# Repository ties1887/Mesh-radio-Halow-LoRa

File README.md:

# Mesh Radio

Open-source 3D-printable radio enclosures for Wi-Fi HaLow, MANET and LoRa experiments.

This repository contains CAD files, printable files, hardware references and short build notes. It is a DIY hardware/CAD release, not a full step-by-step wiring guide. Builders should verify fit, wiring, polarity, cooling, antenna mounting and power setup for their own hardware.

> [!TIP]
> **Support this project**  
> I am a **21-year-old full-time student** building this in my spare time. If this work helps you, donations help fund parts, prototypes and testing.  
> **[Support me on Ko-fi](https://ko-fi.com/ties1887)**

## Contents

- [Choose your build](#choose-your-build)
- [Standalone battery pack](#standalone-battery-pack)
- [What the files are for](#what-the-files-are-for)
- [Build notes](#build-notes)
- [Bill of materials](#bill-of-materials)
- [Planned builds](#planned-builds)
- [Software](#software)
- [Contributing and support](#contributing-and-support)
- [License](#license)

## Choose your build

| Build | Generation | Main hardware | Files |
|---|---|---|---|
| **[P4-Wio](./Second-Generation-Builds/P4-Wio/)** | Second generation | Raspberry Pi 4 + WM1302 Pi HAT + Wio-WM6108 | 3MF, STEP, SolidWorks 2025 |
| **[CM4 Carrier Board](./Second-Generation-Builds/CM4-Carrier-Board/)** | Second generation, development | Raspberry Pi CM4 + M.2 E-key Wi-Fi + optional MM8108 HaLow | KiCad source, local libraries, 3D models, review report |
| **[V3](./First-Generation-Builds/V3_18-6-2026/)** | First generation | Raspberry Pi 4 + WM1302 Pi HAT + Wio-WM6108 + RAK WisMesh 1W kit | 3MF, STEP, SolidWorks 2023/2025 |
| **[V2](./First-Generation-Builds/V2_30-5-2026/)** | First generation | Raspberry Pi 4 + WM1302 Pi HAT + Wio-WM6108 + RAK WisMesh 1W kit | 3MF, STL, STEP, SolidWorks 2023/2025 |
| **[V1](./First-Generation-Builds/V1_5-5-2026/)** | First generation | Raspberry Pi 4 + WM1302 Pi HAT + Wio-WM6108 + RAK WisMesh 1W kit | 3MF, STEP, SolidWorks 2023/2025 |

V1, V2 and V3 are still valid first generation builds. They may need more fitting or manual finishing, but they have been built, printed and used.

> [!CAUTION]
> **HaLow and LoRa together:** early tests with Wi-Fi HaLow and LoRa/Meshtastic running at the same time did not work well. The radios appeared to interfere with each other, even when using different channels. These tests were limited, so this is not a final RF conclusion, but builders should not expect HaLow and LoRa to work perfectly together without extra testing or design changes. Treat LoRa as a fallback/secondary system unless you have verified your own setup.

## Standalone battery pack

The **[Twist-Lock Battery Pack](./Twist-Lock-Battery-Pack/)** is a separate design, not part of only one build.

It is intended as a shared battery-pack design for both:

- first generation builds;
- second generation builds.

Available files include 3MF, STEP, STL and SolidWorks 2025 source archive.

## What the files are for

| File type | Use |
|---|---|
| `3MF` | Preferred print/project files for slicers |
| `STL` | Individual mesh exports when available |
| `STEP` | CAD exchange files for inspection, remixing or non-SolidWorks workflows |
| `SolidWorks` / `.zip` | Native source files or complete SolidWorks archives |

Download the complete build folder before opening a SolidWorks assembly so referenced parts remain available.

## Build notes

- **P4-Wio** is the current second generation build. It uses a Raspberry Pi 4, WM1302 Pi HAT style adapter and Seeed Studio Wio WM6108 Wi-Fi HaLow module.
- **P4-Wio is HaLow-only.** It does not include the separate LoRa/Meshtastic subsystem from the first generation prototypes.
- **V1** uses an integrated battery layout.
- **V2 and V3** use a removable twist-lock battery layout.
- **CM4 Carrier Board** source files are available for review and collaboration, but the design is not yet released for fabrication. Read its production-check report before making hardware.

<details>
<summary><strong>Prototype component and power-flow reference</strong></summary>

<br>

This is a prototype reference for component relationships and power flow. It combines ideas from different versions and is not a final wiring guide.

</details>

<details>
<summary><strong>Prototype wiring reference</strong></summary>

<br>

This image documents prototype wiring. Verify every connection against the exact version and modules you are building.

</details>

## Bill of materials

The shared BOM contains parts used across multiple prototypes. **Do not order every listed part.** Check the build you are making first.

**[Open the current shared BOM](https://docs.google.com/spreadsheets/d/1Nt8EjYsgWTId0Qjl1BAAxPci3bh1FSZ7VQxQRFxyHnk/edit?usp=sharing)**

Supplier links, prices and availability may change. Confirm dimensions, connector type, voltage range and module version before ordering.

## Planned builds

<details>
<summary><strong>Future build names and targets</strong></summary>

<br>

| Build | Hardware target | Notes |
|---|---|---|
| `P4-LongWave` | Raspberry Pi 4 + Lunpid/LongWave MM8108 USB HaLow | Planned Pi 4 USB HaLow build |
| `C4-LongWave` | Raspberry Pi CM4 + Lunpid/LongWave MM8108 USB HaLow | Planned compact CM4 build |
| `C4-DualMesh` | Raspberry Pi CM4 + MM8108 HaLow + MT7916EUD | Research path for HaLow plus 2.4/5/6 GHz mesh |

```text
P4 = Raspberry Pi 4
C4 = Raspberry Pi Compute Module 4
Wio = Seeed Studio Wio WM6108 HaLow
LongWave = Lunpid/LongWave MM8108 USB HaLow
DualMesh = MM8108 HaLow plus MT7916EUD for 2.4/5/6 GHz mesh
```

A planned build should get its own folder when it has a selected hardware stack, CAD layout, printable/exported files and a short build README.

</details>

## Software

Software installation and support are provided by the upstream projects:

- **[OpenMANET documentation](https://openmanet.github.io/docs/)**
- **[OpenMANET firmware](https://github.com/OpenMANET/firmware)**
- **[Meshtastic documentation](https://meshtastic.org/docs/)**
- **[Meshtastic firmware](https://github.com/meshtastic/firmware)**

OpenMANET, Meshtastic and third-party hardware remain subject to their own licenses, documentation and support policies.

## Contributing and support

Questions, measurements, test results, issue reports, documentation corrections and design improvements are welcome.

- **[Open an issue](https://github.com/ties1887/Mesh-radio-Halow-LoRa/issues)**
- **[Create a pull request](https://github.com/ties1887/Mesh-radio-Halow-LoRa/pulls)**
- **Support the project:** https://ko-fi.com/ties1887
- **Contact:** Discord `ties1887`

Thank you to everyone who supports the project with feedback, testing, tips, donations or useful hardware/design suggestions.

## License

This repository is released under the **[Creative Commons Attribution-NonCommercial-ShareAlike 4.0 International License](./LICENSE)** (**CC BY-NC-SA 4.0**).

You may copy, build, modify and share the designs for personal, educational and non-commercial community use. You may not sell these designs, sell printed parts based on these designs, or use them commercially without written permission from the author.

Private modifications are allowed and do not need to be uploaded or published. If you share modified files publicly, they must stay under the same non-commercial share-alike license.

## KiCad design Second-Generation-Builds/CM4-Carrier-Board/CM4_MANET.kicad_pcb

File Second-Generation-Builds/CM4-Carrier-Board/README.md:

# CM4 MANET carrier board

KiCad source project for the experimental Raspberry Pi Compute Module 4 MANET carrier board.

> [!WARNING]
> **Development design — not released for fabrication.** The current production review still lists unresolved ERC, GND-connectivity, SI/PI, mechanical and manufacturing-output items. Read [`docs/PRODUCTIECHECK-2026-09-19.md`](./docs/PRODUCTIECHECK-2026-09-19.md) before using the design.

## Hardware target

The carrier combines:

- Raspberry Pi Compute Module 4;
- M.2 E-key Wi-Fi/MANET radio interface;
- onboard Morse Micro MM8108 HaLow option;
- USB2514B USB hub and two external USB interfaces;
- microSD, Ethernet, power regulation and service interfaces;
- Pololu D42V55F5 5 V regulator module.

## Open the project

1. Install **KiCad 10** or newer.
2. Download or clone this complete folder so the local libraries and 3D models remain beside the project.
3. Open [`CM4_MANET.kicad_pro`](./CM4_MANET.kicad_pro).
4. KiCad should resolve the bundled libraries through [`sym-lib-table`](./sym-lib-table) and [`fp-lib-table`](./fp-lib-table).

The project uses KiCad's standard symbol, footprint and 3D libraries in addition to the bundled local files.

## Included files

| Path | Purpose |
|---|---|
| `CM4_MANET.kicad_pro` | KiCad project settings and design rules |
| `CM4_MANET.kicad_sch` | Hierarchical top-level schematic |
| `01_…16_*.kicad_sch` | Schematic sheets |
| `CM4_MANET.kicad_pcb` | Routed six-layer PCB |
| `MANET.kicad_sym` | Bundled project symbols |
| `MANET.pretty/` | Bundled project footprints |
| `G2401CE.kicad_sym` | Ethernet magnetics symbol |
| `G2401CE.pretty/` | Ethernet magnetics footprint |
| `models/`, `G2401CE.3dshapes/` | Local 3D models referenced by the board |
| `docs/PLAN-EN-STATUS.md` | Canonical design context and decisions |
| `docs/PRODUCTIECHECK-2026-09-19.md` | Latest production-readiness review and correction checklist |
| `DATASHEET-INDEX-V0.11.md` | Component/source index |

## Verified source snapshot

The upload was prepared from the latest saved and synchronized project snapshot available on 19 September 2026.

| File | SHA-256 |
|---|---|
| `CM4_MANET.kicad_pro` | `29031d407538b3dbcb6472aa7c64797e4d6ba71f1556e2ef84310c6bf45d1d5d` |
| `CM4_MANET.kicad_sch` | `d8fc85620186ded0c0d289be1d9e3905773756102ce121de9318bc477c56a758` |
| `CM4_MANET.kicad_pcb` | `218439d0e7e71eeba17b0bce05ddc644826dbbb2ce876aa322ecba9a2478592e` |

## Deliberately not included

The following local files were excluded because they are stale, generated, machine-specific or not needed to inspect/edit the source:

- old Gerbers and drill files;
- old BOM/CPL quotation exports;
- old STEP assembly export;
- KiCad lock/preferences files;
- temporary validation output;
- `.history`, caches and backups;
- local copies of third-party datasheets.

Generate new fabrication files only after the correction checklist is closed and the design has passed a fresh production review.

## License

This folder follows the repository license: [CC BY-NC-SA 4.0](../../LICENSE).

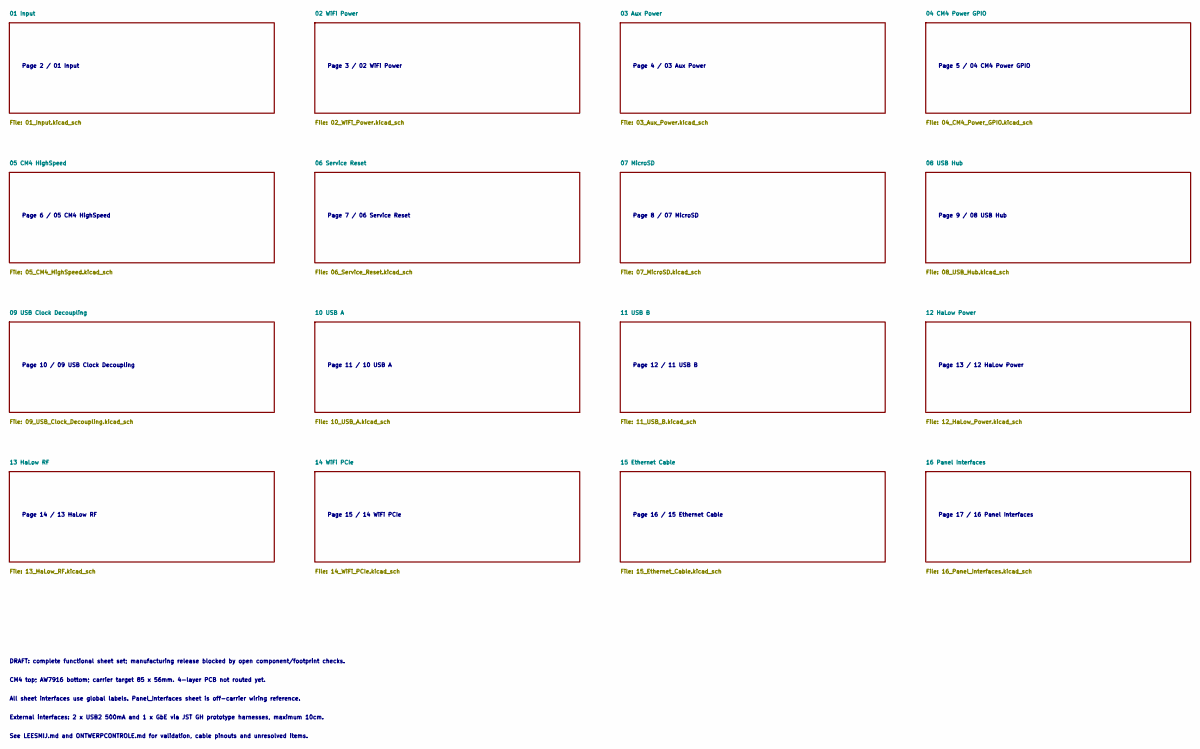
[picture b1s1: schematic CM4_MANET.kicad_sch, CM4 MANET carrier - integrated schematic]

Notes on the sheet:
DRAFT: complete functional sheet set; manufacturing release blocked by open component/footprint checks.
Page 11 / 10 USB A
CM4 top; AW7916 bottom; carrier target 85 x 56mm. 4-layer PCB not routed yet.
Page 4 / 03 Aux Power
Page 16 / 15 Ethernet Cable
Page 8 / 07 MicroSD
Page 5 / 04 CM4 Power GPIO
Page 15 / 14 WiFi PCIe
Page 12 / 11 USB B
Page 9 / 08 USB Hub
Page 17 / 16 Panel Interfaces
Page 14 / 13 HaLow RF
External interfaces: 2 x USB2 500mA and 1 x GbE via JST GH prototype harnesses, maximum 10cm.
Page 2 / 01 Input
Page 13 / 12 HaLow Power
See LEESMIJ.md and ONTWERPCONTROLE.md for validation, cable pinouts and unresolved items.
Page 7 / 06 Service Reset
All sheet interfaces use global labels. Panel_Interfaces sheet is off-carrier wiring reference.
Page 3 / 02 WiFi Power
Page 10 / 09 USB Clock Decoupling
Page 6 / 05 CM4 HighSpeed

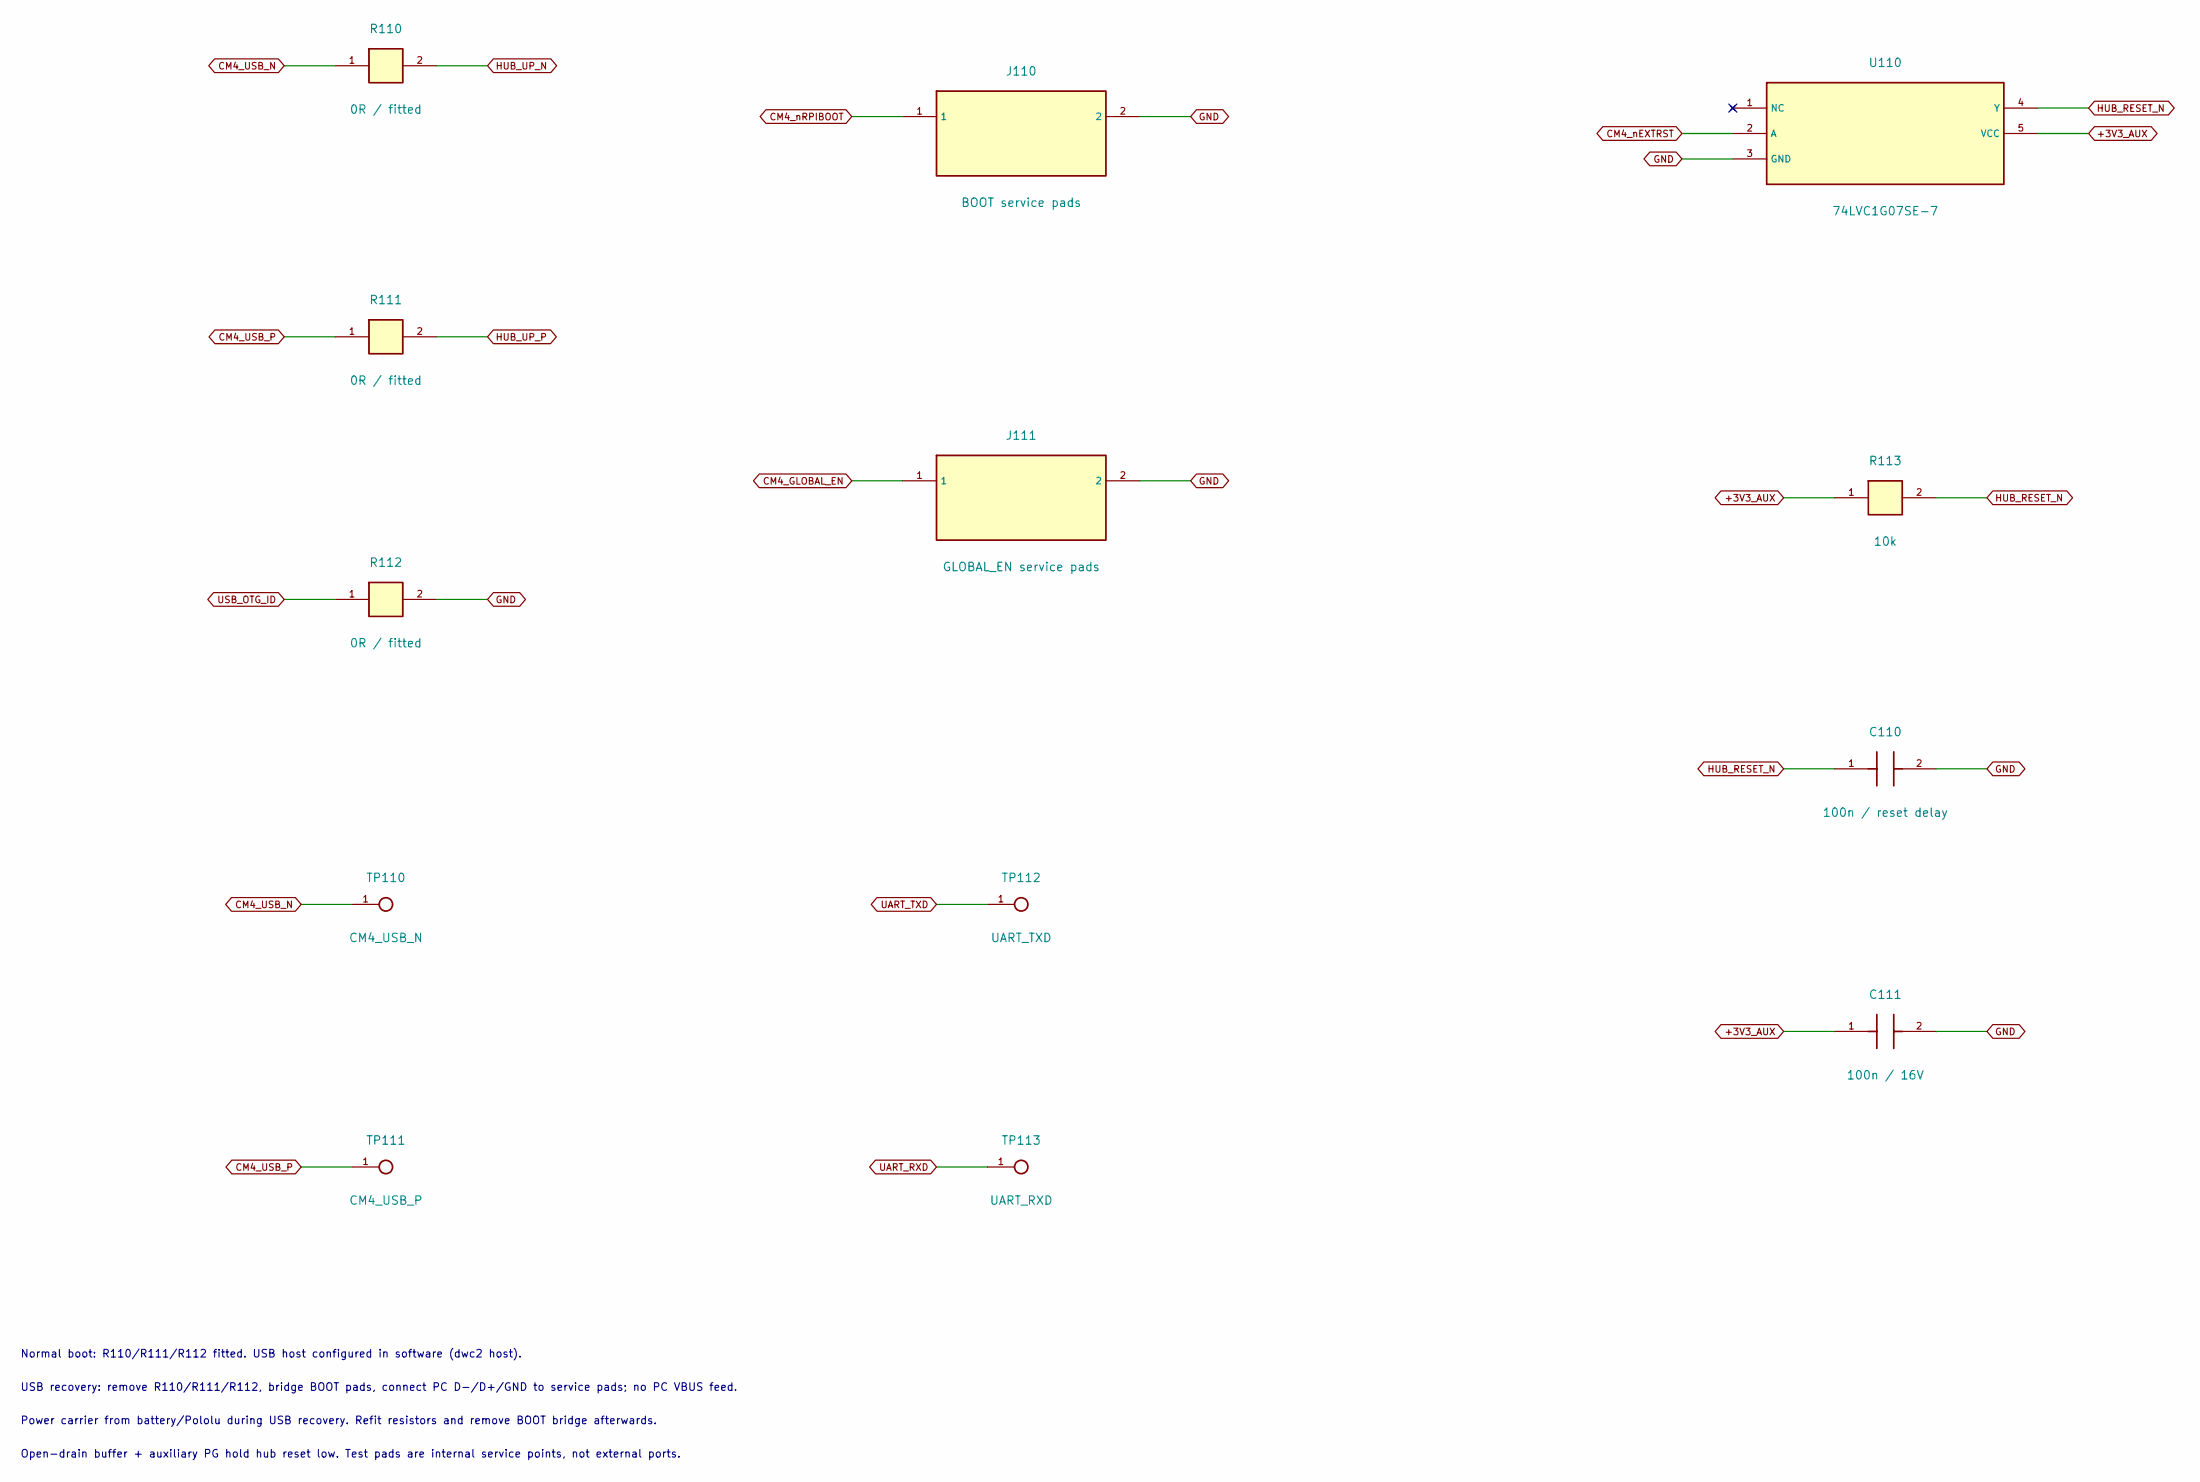
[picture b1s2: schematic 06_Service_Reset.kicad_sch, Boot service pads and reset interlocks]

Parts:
C110: 100n / reset delay; C_0603_1608Metric; MPN CL10B104KB8NNNC; LCSC C1591
C111: 100n / 16V; C_0603_1608Metric; MPN CL10B104KB8NNNC; LCSC C1591
J110: BOOT service pads; Service_Pads; JLCPCB Status EXCLUDE_FROM_JLCPCB_ASSEMBLY
J111: GLOBAL_EN service pads; Service_Pads; JLCPCB Status EXCLUDE_FROM_JLCPCB_ASSEMBLY
R110, R111, R112: 0R / fitted; R_0603_1608Metric; MPN 0603WAF0000T5E; LCSC C21189
R113: 10k; R_0603_1608Metric; MPN 0603WAF1002T5E; LCSC C25804
TP110: CM4_USB_N; TestPoint_Pad_D1.5mm; JLCPCB Status EXCLUDE_FROM_JLCPCB_ASSEMBLY
TP111: CM4_USB_P; TestPoint_Pad_D1.5mm; JLCPCB Status EXCLUDE_FROM_JLCPCB_ASSEMBLY
TP112: UART_TXD; TestPoint_Pad_D1.5mm; JLCPCB Status EXCLUDE_FROM_JLCPCB_ASSEMBLY
TP113: UART_RXD; TestPoint_Pad_D1.5mm; JLCPCB Status EXCLUDE_FROM_JLCPCB_ASSEMBLY
U110: 74LVC1G07SE-7; SOT-353_SC-70-5; MPN 74LVC1G07SE-7; LCSC C67531

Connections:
+3V3_AUX: C111.1, R113.1, U110.5 (VCC); also elsewhere on the board
CM4_GLOBAL_EN: J111.1; also elsewhere on the board
CM4_USB_N: R110.1, TP110.1; also elsewhere on the board
CM4_USB_P: R111.1, TP111.1; also elsewhere on the board
CM4_nEXTRST: U110.2 (A); also elsewhere on the board
CM4_nRPIBOOT: J110.1; also elsewhere on the board
GND: C110.2, C111.2, J110.2, J111.2, R112.2, U110.3 (GND); also elsewhere on the board
HUB_RESET_N: C110.1, R113.2, U110.4 (Y); also elsewhere on the board
HUB_UP_N: R110.2; also elsewhere on the board
HUB_UP_P: R111.2; also elsewhere on the board
UART_RXD: TP113.1; also elsewhere on the board
UART_TXD: TP112.1; also elsewhere on the board
USB_OTG_ID: R112.1; also elsewhere on the board

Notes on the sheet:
Open-drain buffer + auxiliary PG hold hub reset low. Test pads are internal service points, not external ports.
Normal boot: R110/R111/R112 fitted. USB host configured in software (dwc2 host).
Power carrier from battery/Pololu during USB recovery. Refit resistors and remove BOOT bridge afterwards.
USB recovery: remove R110/R111/R112, bridge BOOT pads, connect PC D-/D+/GND to service pads; no PC VBUS feed.

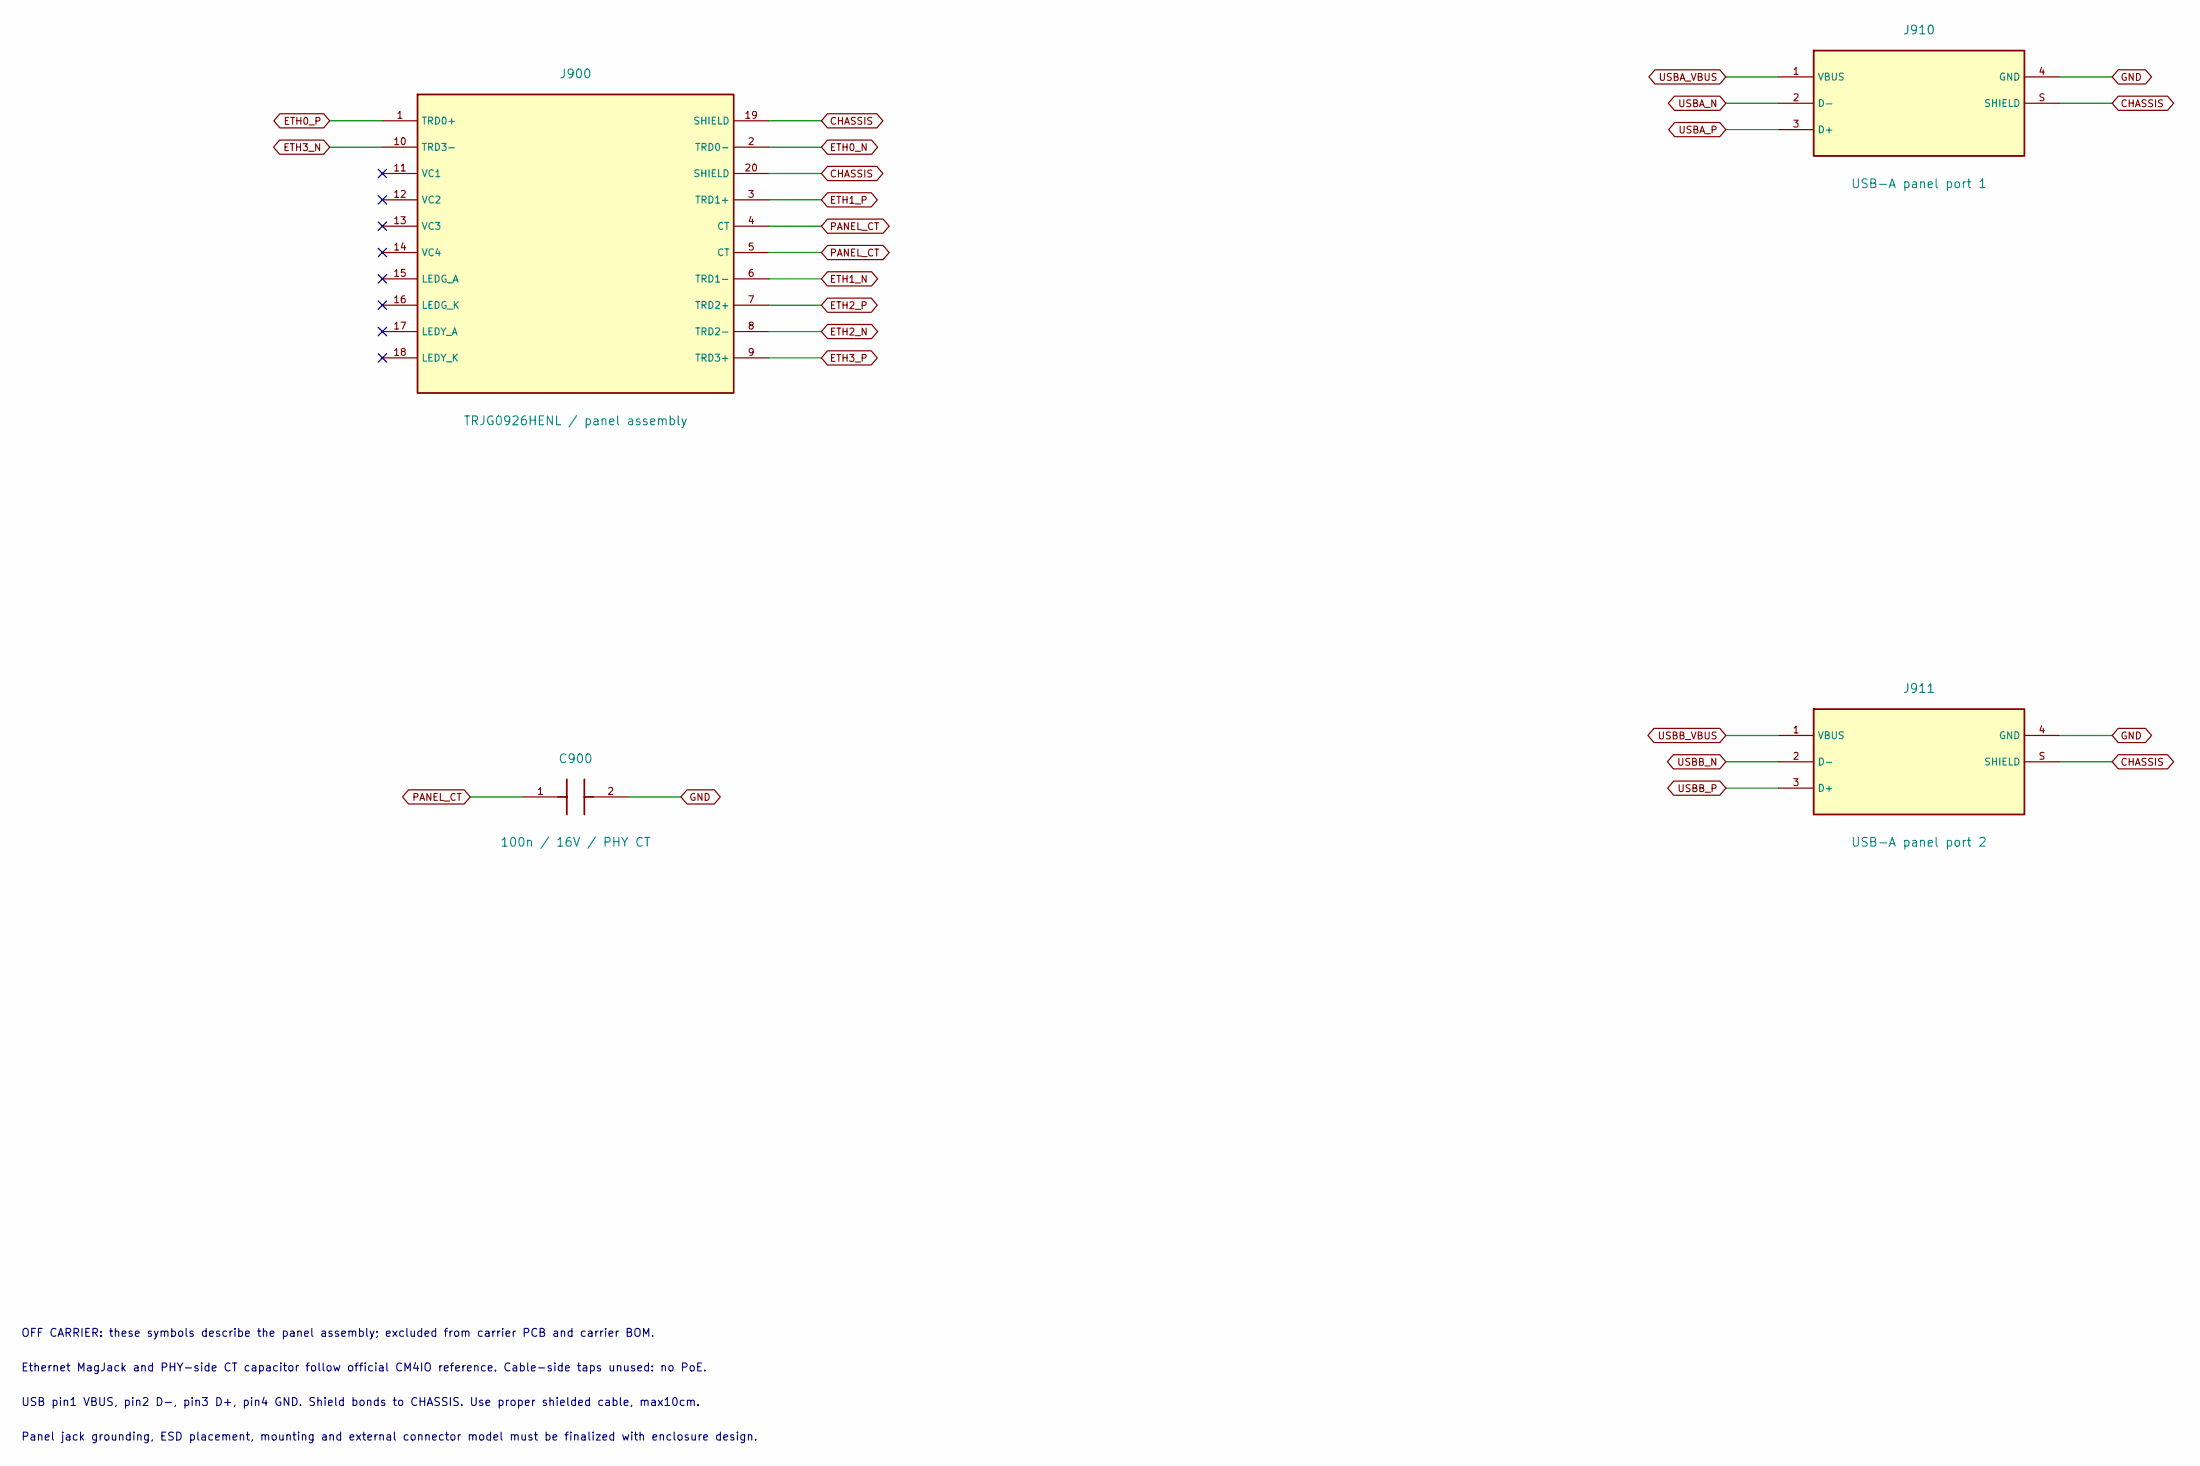
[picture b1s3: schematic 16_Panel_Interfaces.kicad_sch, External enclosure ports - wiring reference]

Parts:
C900: 100n / 16V / PHY CT; C_0603_1608Metric; JLCPCB Status EXCLUDE_FROM_JLCPCB_ASSEMBLY
J900: TRJG0926HENL / panel assembly; JLCPCB Status EXCLUDE_FROM_JLCPCB_ASSEMBLY
J910: USB-A panel port 1; JLCPCB Status EXCLUDE_FROM_JLCPCB_ASSEMBLY
J911: USB-A panel port 2; JLCPCB Status EXCLUDE_FROM_JLCPCB_ASSEMBLY

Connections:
unnamed: C900.1, J900.4 (CT), J900.5 (CT)
unnamed: C900.2, J910.4 (GND), J911.4 (GND)
unnamed: J900.19 (SHIELD), J900.20 (SHIELD), J910.S (SHIELD), J911.S (SHIELD)

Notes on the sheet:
Ethernet MagJack and PHY-side CT capacitor follow official CM4IO reference. Cable-side taps unused: no PoE.
Panel jack grounding, ESD placement, mounting and external connector model must be finalized with enclosure design.
USB pin1 VBUS, pin2 D-, pin3 D+, pin4 GND. Shield bonds to CHASSIS. Use proper shielded cable, max10cm.
OFF CARRIER: these symbols describe the panel assembly; excluded from carrier PCB and carrier BOM.

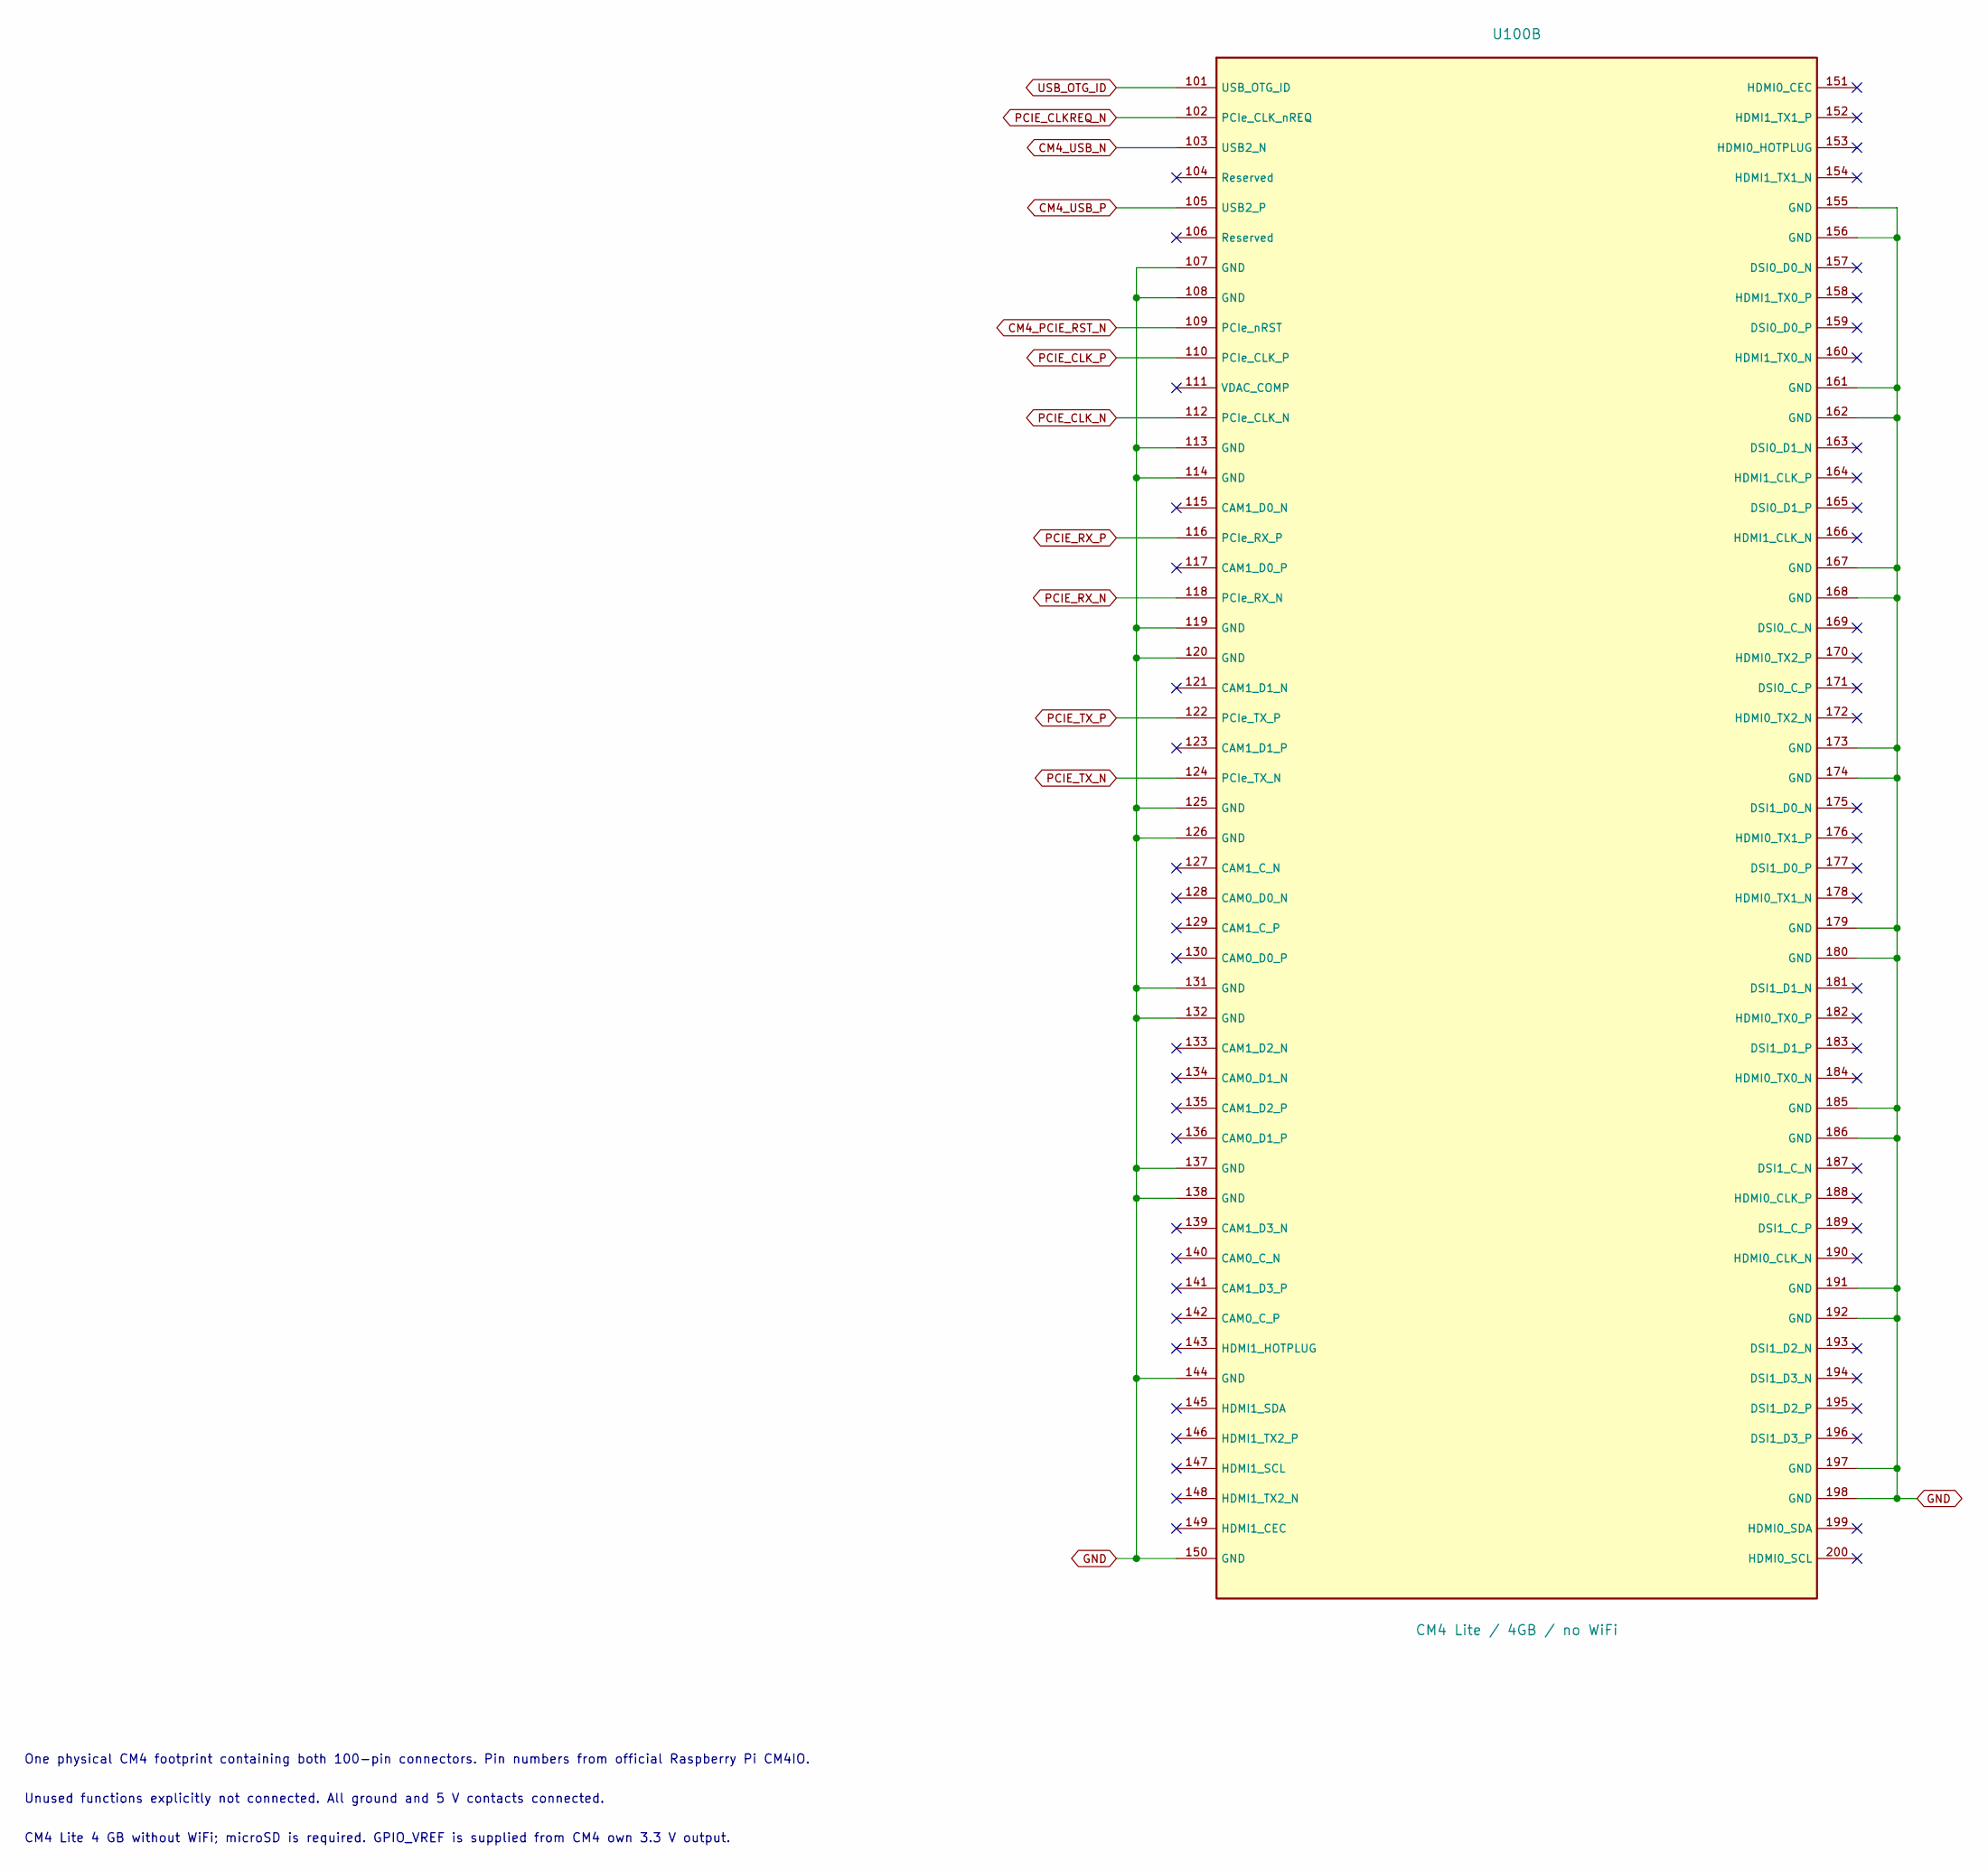
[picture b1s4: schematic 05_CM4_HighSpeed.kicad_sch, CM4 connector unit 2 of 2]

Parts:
U100: CM4 Lite / 4GB / no WiFi; Raspberry-Pi-4-Compute-Module; JLCPCB Status EXCLUDE_FROM_JLCPCB_ASSEMBLY

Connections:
CM4_PCIE_RST_N: U100.109 (PCIe_nRST); also elsewhere on the board
CM4_USB_N: U100.103 (USB2_N); also elsewhere on the board
CM4_USB_P: U100.105 (USB2_P); also elsewhere on the board
GND: U100.107 (GND), U100.108 (GND), U100.113 (GND), U100.114 (GND), U100.119 (GND), U100.120 (GND), U100.125 (GND), U100.126 (GND), U100.131 (GND), U100.132 (GND), U100.137 (GND), U100.138 (GND), U100.144 (GND), U100.150 (GND), U100.155 (GND), U100.156 (GND), U100.161 (GND), U100.162 (GND), U100.167 (GND), U100.168 (GND), U100.173 (GND), U100.174 (GND), U100.179 (GND), U100.180 (GND), U100.185 (GND), U100.186 (GND), U100.191 (GND), U100.192 (GND), U100.197 (GND), U100.198 (GND); also elsewhere on the board
PCIE_CLKREQ_N: U100.102 (PCIe_CLK_nREQ); also elsewhere on the board
PCIE_CLK_N: U100.112 (PCIe_CLK_N); also elsewhere on the board
PCIE_CLK_P: U100.110 (PCIe_CLK_P); also elsewhere on the board
PCIE_RX_N: U100.118 (PCIe_RX_N); also elsewhere on the board
PCIE_RX_P: U100.116 (PCIe_RX_P); also elsewhere on the board
PCIE_TX_N: U100.124 (PCIe_TX_N); also elsewhere on the board
PCIE_TX_P: U100.122 (PCIe_TX_P); also elsewhere on the board
USB_OTG_ID: U100.101 (USB_OTG_ID); also elsewhere on the board

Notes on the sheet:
One physical CM4 footprint containing both 100-pin connectors. Pin numbers from official Raspberry Pi CM4IO.
CM4 Lite 4 GB without WiFi; microSD is required. GPIO_VREF is supplied from CM4 own 3.3 V output.
Unused functions explicitly not connected. All ground and 5 V contacts connected.

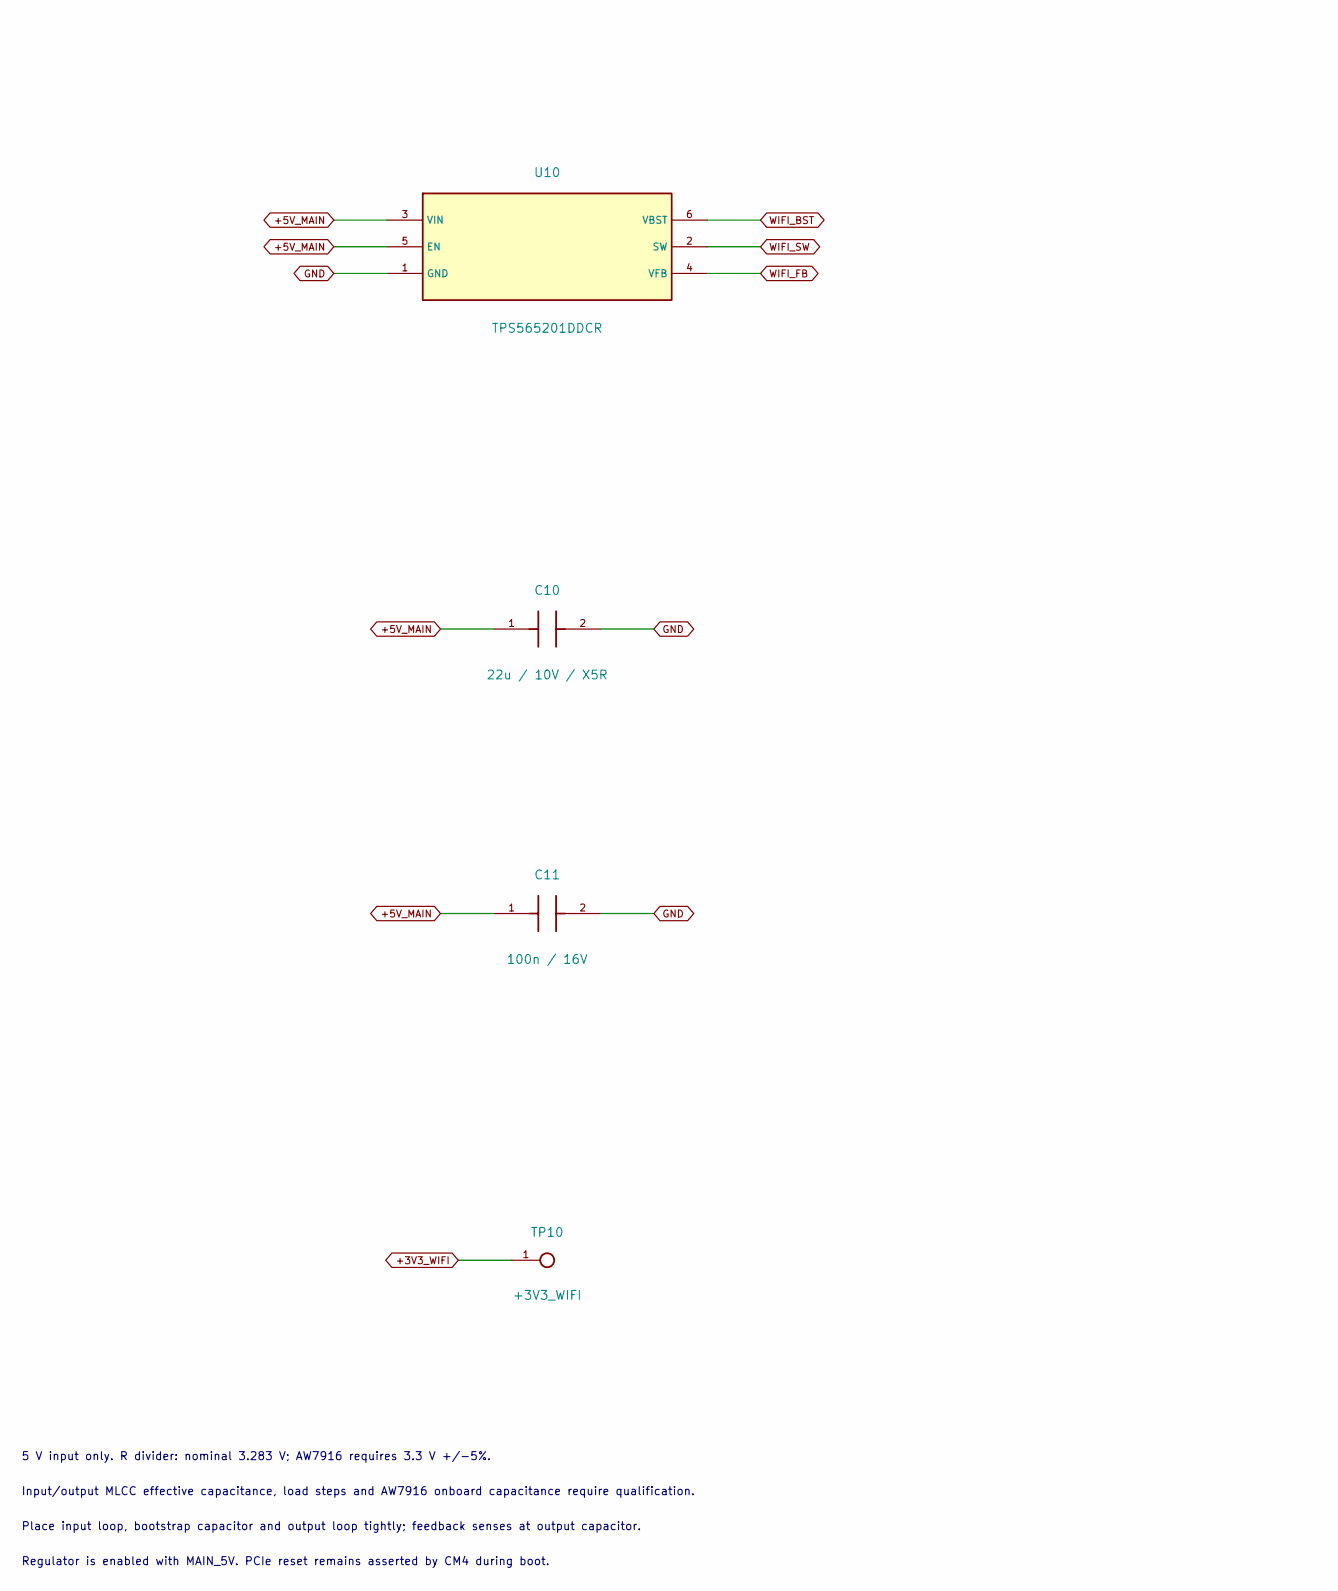
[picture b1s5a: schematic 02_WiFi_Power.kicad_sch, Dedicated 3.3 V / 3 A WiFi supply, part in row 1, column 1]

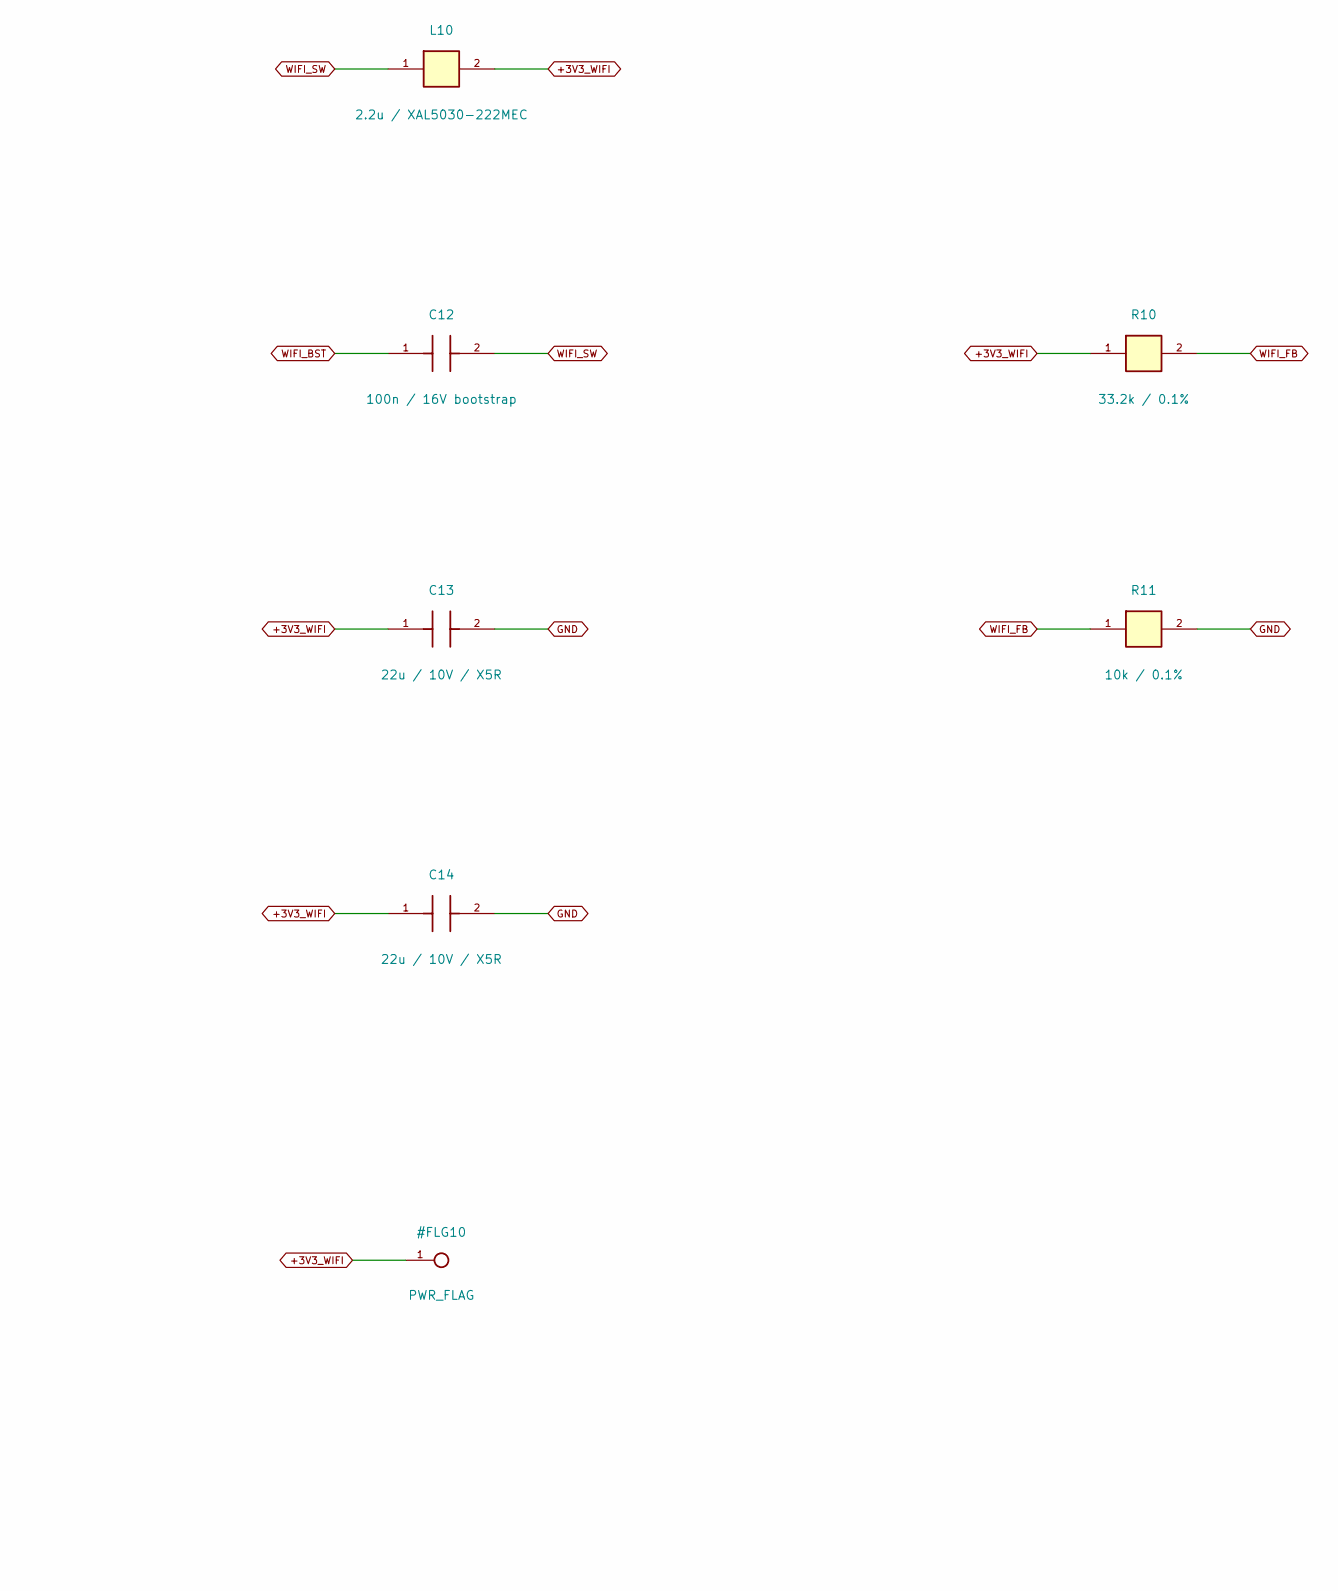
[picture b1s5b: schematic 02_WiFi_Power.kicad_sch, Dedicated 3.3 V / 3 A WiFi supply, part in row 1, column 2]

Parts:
C10, C13, C14: 22u / 10V / X5R; C_1206_3216Metric; MPN 1206X226K160NT; LCSC C105480
C11: 100n / 16V; C_0603_1608Metric; MPN CL10B104KB8NNNC; LCSC C1591
C12: 100n / 16V bootstrap; C_0603_1608Metric; MPN CL10B104KB8NNNC; LCSC C1591
L10: 2.2u / XAL5030-222MEC; L_Coilcraft_XAL5030-XXX; MPN XAL5030-222MEC; LCSC C920280
R10: 33.2k / 0.1%; R_0603_1608Metric; MPN TNPW060333K2BEEA; LCSC C2075328
R11: 10k / 0.1%; R_0603_1608Metric; MPN PTFR0603B10K0P9; LCSC C328421
TP10: +3V3_WIFI; TestPoint_Pad_D1.5mm; JLCPCB Status EXCLUDE_FROM_JLCPCB_ASSEMBLY
U10: TPS565201DDCR; SOT-23-6; MPN TPS565201DDCR; LCSC C327676

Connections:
+3V3_WIFI: C13.1, C14.1, L10.2, R10.1, TP10.1; also elsewhere on the board
+5V_MAIN: C10.1, C11.1, U10.3 (VIN), U10.5 (EN); also elsewhere on the board
GND: C10.2, C11.2, C13.2, C14.2, R11.2, U10.1 (GND); also elsewhere on the board
WIFI_BST: C12.1, U10.6 (VBST)
WIFI_FB: R10.2, R11.1, U10.4 (VFB)
WIFI_SW: C12.2, L10.1, U10.2 (SW)

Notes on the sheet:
Regulator is enabled with MAIN_5V. PCIe reset remains asserted by CM4 during boot.
Input/output MLCC effective capacitance, load steps and AW7916 onboard capacitance require qualification.
5 V input only. R divider: nominal 3.283 V; AW7916 requires 3.3 V +/-5%.
Place input loop, bootstrap capacitor and output loop tightly; feedback senses at output capacitor.

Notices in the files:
hardware/pcb/cm4-manet-carrier/work/sources/cm4io/CM4IOv5.kicad_sch:
© 2020-2022 Raspberry Pi Ltd (formerly Raspberry Pi (Trading) Ltd.)
